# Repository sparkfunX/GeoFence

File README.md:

# GeoFence
A device to monitor when it is inside or outside various GPS waypoints.

# The GeoFence App is no longer supported
Unfortunately, Google has changed the way that they bill their Maps API and because we're no longer building the GeoFence hardware, 
we won't be updating the software. If you're looking for a way to create and enforce your own geofences, we encourage you to check out the [uBlox](https://learn.sparkfun.com/tutorials/getting-started-with-u-center-for-u-blox) products we now carry. If you still have a GeoFence board that you'd like to continue using, you have two options:

1. You can aqcuire your own [Google Maps API Key](https://developers.google.com/maps/documentation/javascript/get-api-key), 
replace our key string in the app source code (index.html line 77), and recompile the app in [electronjs](https://electronjs.org/).

2. You can construct your own configuration string using lat-long data from the source of your choosing and send it to the board using 
a serial terminal. Configuration strings are constructed as follows:

## Complete Configuration String

| Header | Zone 1 | Zone 2 | Zone 3 | Zone 4 | Footer | Chksum | Terminator |
| ------ | ------ | ------ | ------ | ------ | ------ | ------ | ---------- |
| "$\n"  |        |        |        |        |  "^\n" |        |     "$"    |

## Zone Configuration

### Null Zone
The device expects to see configurations for each zone, even if the zone is "unprogrammed". Unprogrammed zones are marked with the "X" flag.

| Header |
| ------ |
|  "X\n" |

### Rectangular Zone
Rectangular Boundaries are defined by their NorthEast and SouthWest corners. The Latitude and Longitude of each corner is fixed to 
6 digits of precision after the decimal. Rectangular Zones are marked with the "R" Flag.

| Header | NorthEast Lat | NorthEast Long | SouthWest Lat | SouthWest Long | 
| ------ | ------------- | -------------- | ------------- | -------------- |
|  "R\n" | "xx.xxxxxx\n" |  "-x.xxxxxx\n" | "xxx.xxxxxx\n"| "xx.xxxxxx\n"  |

### Circular Zone
Circular Boundaries are defined by their center coordinate and their radius in meters, rounded to the nearest meter. 
Circular Zones are marked with the "C" flag.

| Header | Center Lat | Center Long | Radius Meters | 
| ------ | ---------- | ----------- | ------------- | 
|  "C\n" |"x.xxxxxx\n"|"-x.xxxxxx\n"|    "xxx\n"    |

### Checksum
Strings are transmitted with a checksum for integrity. The checksum is the sum of all character values in the string up to 
the checksum, modulo 256. It is calculated in the App thusly: 

```
  for(var i = 0; i < data.length; i++){
	 chksum = chksum + data.charCodeAt(i); 
  }
  
  chksum = chksum%256;
  ```
  
  The checksum value is written to a single byte and followed by a Line Feed ("\n")
  
### Serial Settings
The configuration string may be sent at any time at 9600 baud. The board will return with "$" if the configuration was succesful, if
the string did not pass checksum, it will return "!"

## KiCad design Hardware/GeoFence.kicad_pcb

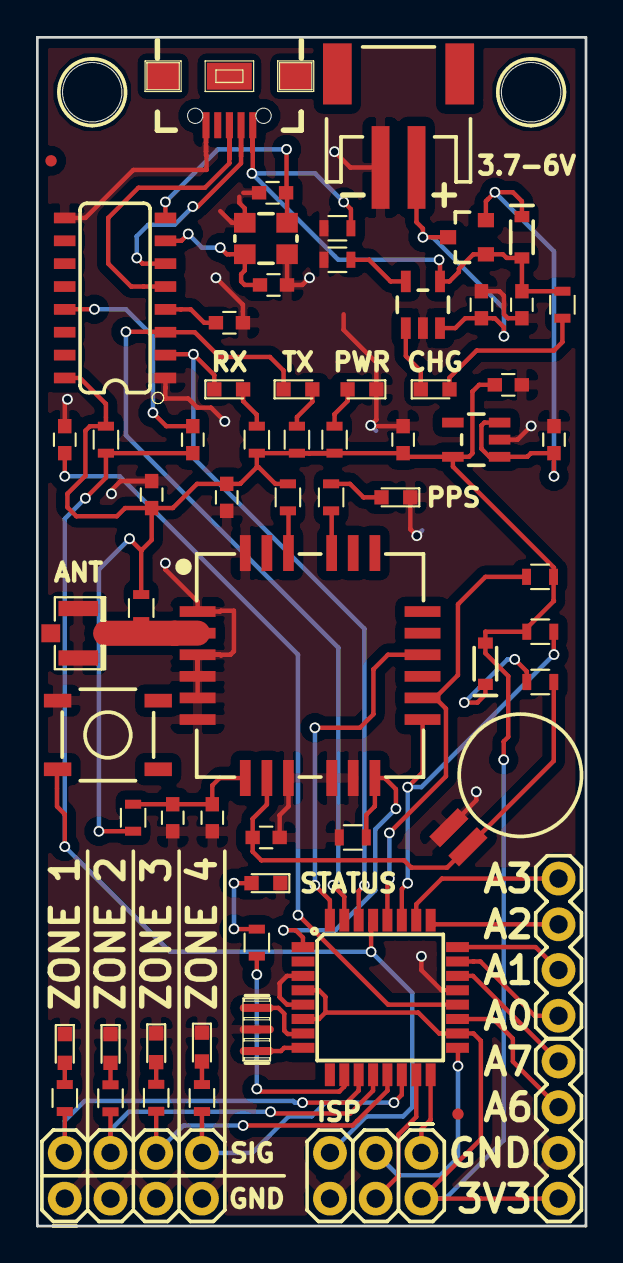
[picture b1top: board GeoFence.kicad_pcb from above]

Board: 2 copper layers, 30.5 x 66.0 mm, 68 parts (0 on the bottom side), 53 nets.

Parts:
B1: COIN CELL; SparkX-6.8MM_COIN_CELL
C1, C2: 10pF; C_0603
C3: 10nF; C_0603
C4, C9, C10, C11, C13: 0.1uF; C_0603
C5, C15: 4.7uF; C_0603
C6, C8, C12, C14: 1.0uF; C_0603
C7: 2.2uF; C_0603
D1, D5, D6, D7, D8, D9: Blue; LED_0603
D2: 0.5A/40V/420mV; SparkFun-DiscreteSemi-SOD-323
D3, D11: Yellow; LED_0603
D4: GREEN; LED_0603
D10: BAT20J; SparkFun-DiscreteSemi-SOD-323
D12: Red; LED_0603
FB1: 600Ohm/100MHz; L_0603
H1, H2: STAND-OFF
J1: U.FL; SparkX-U.FL
J2: microB; USB-B-MICRO-SMD
J3: AVR_SPI_PROG_3X2PTH; 2X3
J4, J5: CONN_04; 1X04
J6: CONN_04X2; 2X4
JP2, JP6: FIDUCIALUFIDUCIAL; FIDUCIAL-MICRO
JP8: LiPo; JST-2-SMD
L1: 33nH/~5%/500mA; L_0603
Q1: 8/16/20MHz; RESONATOR-SMD-3.2X1.3
Q2: 2.5A/30V; SparkFun-DiscreteSemi-SOT23-3
R1, R4, R17, R18: 1k; R_0603
R2, R3, R8, R10, R11, R14, R15: 470; R_0603
R5, R6, R7, R9: 10k; R_0603
R12, R13: 4.7k; R_0603
R16: 2.0k; R_0603
S1: Reset; TACTILE_SWITCH_SMD_5.2MM
U1: TITAN X1 GPS; SparkX-TITAN_X1_GPS
U3: CH340G; SO16
U4: AP2112K-3.3V; SOT23-5
U5: ATMEGA328; TQFP32-08
U6: MCP73831; SOT23-5
Y1: 12MHz; CRYSTAL-SMD-3.2X2.5MM

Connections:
+3V3: C4.1, C7.1, C11.1, C12.1, D2.A, FB1.1, J3.2, J4.1, L1.2, R1.1, R2.2, R6.1, R9.2, R12.2, R13.2, R18.1, U3.16, U4.5, U5.4, U5.6, U5.18
+5V: C15.1, D10.A, J2.VBUS, Q2.1, R5.1, R17.1, U6.4
/A0: J5.1, U5.23
/A1: J5.2, U5.24
/A2: J5.3, U5.25
/A3: J5.4, U5.26
/A6: J4.3, U5.19
/A7: J4.4, U5.22
/ATRESET: C9.1, J3.5, R6.2, S1.3, U5.29
/BACKUP: B1.+, C8.1, R4.2, U1.8
/D7: J6.2, R8.1, U5.11
/D8: J6.4, R10.1, U5.12
/D9: J6.6, R11.1, U5.13
/D10: J6.8, R14.1, U5.14
/DTR: C9.2, U3.13
/INT: U1.16, U5.32
/MISO: J3.1, U5.16
/MOSI: J3.4, U5.15
/PPS: R3.2, U1.21
/RXI: D4.1, U3.2, U5.30
/SCK: J3.3, U5.17
/SCL: R12.1, U1.14, U5.28
/SDA: R13.1, U1.13, U5.27
/STATUS: R15.2, U5.10
/TXO: D3.1, U3.3, U5.31
/WAKE: R7.1, U1.12, U5.1
/~RESET: R9.1, U1.22
GND: B1.-, C1.2, C2.2, C3.2, C4.2, C5.2, C6.2, C7.2, C8.2, C10.2, C11.2, C12.2, C13.2, C14.2, C15.2, D1.1, D5.1, D6.1, D7.1, D8.1, D9.1, D12.1, J1.1, J1.2, J2.GND, J3.6, J4.2, J6.1, J6.3, J6.5, J6.7, JP8.1, Q1.2, R5.2, R7.2, R16.2, S1.1, U1.1, U1.3, U1.4, U1.5, U1.6, U1.9, U1.10, U1.11, U1.24, U3.1, U3.9, U4.2, U5.3, U5.5, U5.21, U6.2, Y1.2, Y1.4
unnamed: C1.1, U3.7, Y1.3
unnamed: C2.1, U3.8, Y1.1
unnamed: C3.1, U3.4
unnamed: C6.1, D10.C, Q2.2, U4.1, U4.3
unnamed: C10.1, U5.20
unnamed: C13.1, C14.1, FB1.2, U1.7
unnamed: D1.2, R3.1
unnamed: D2.C, R4.1
unnamed: D3.2, R1.2
unnamed: D4.2, R2.1
unnamed: D5.2, R8.2
unnamed: D6.2, R10.2
unnamed: D7.2, R11.2
unnamed: D8.2, R14.2
unnamed: D9.2, R15.1
unnamed: D11.1, U6.1
unnamed: D11.2, R17.2
unnamed: D12.2, R18.2
unnamed: J1.FEED, L1.1, U1.2
unnamed: J2.D+, U3.5
unnamed: J2.D-, U3.6
unnamed: Q1.1, U5.7
unnamed: Q1.3, U5.8
unnamed: R16.1, U6.5
V_BATT: C5.1, JP8.2, Q2.3, U6.3

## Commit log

2017-06-16 :neckbeard: Added .gitattributes & .gitignore files
2017-06-23 Finished Schematic
    Got the rest of the EAGLE to KiCad conversions done and got everything
    airwired properly (Hell is a real place called "CvPcb"). Beginnings of a
    layout are happening now.
2017-06-26 Moved Reference labels to drwg layer
    The board layout is beginning to take form
2017-06-27 Routing
    Started Routing
2017-06-27 Ready for Review
2017-06-29 Design Review Changes
2017-06-29 Ready for Panelization
2017-06-29 Ready for Panelization
    For real this time, though
2017-06-29 Panelized
2017-07-05 Panel Update
2017-07-10 Adding tester firmware
2017-07-10 Upload Firmware
2017-07-10 Sharing the Software and Firmware
2017-07-13 Removing extra init code from GeoFence
2017-07-13 Adding STAT LED indicator modes
2017-07-13 Adding SIV indication
2017-07-17 Adding nan catch, sets EEPROM to 0.0 at first power on.
2017-07-17 Adding system valid pin
    When we have a lock, push pin A0 to high. When not valid, A0 is low.
2017-07-17 Adding startup and download indication to zone LEDs
    Zone LEDs will blink cylon when power up or when new data is downloaded.
2017-07-17 Zones now blink when receive data successful
2017-07-17 Removing heartbeat. Removing SIV indication before lock.
2017-07-31 Formware fix
    Properly zeroes unused EEPROM bytes and alerts user when no zones are
    programmed.
2017-07-31 Software Fixes
    Added a button to close the active serial port as well as a 3 second
    lockout on the config button after opening the port (to allow device
    time to reset)
2017-08-01 No changes
    I opened the project files so they were altered.
2017-08-03 Config Success Alert Box added to software
    Also status bar messages persist for 5 seconds. We're now on v0.1.1
2017-08-03 Removed headers from paste layer / New Gerbers
2018-03-26 Updated Source and Rebuilt BINs to v0.1.2
    Now built against electron 1.8.2-beta.5 to Address CVE-2018-1000118
